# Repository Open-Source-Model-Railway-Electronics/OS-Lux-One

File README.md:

# OS-Lux-One

The OS-Lux-One is an open-source modular LED lighting strip for digital model railway systems 
It replaces multiple fixed-length coach strips with one universal version that can be shortened and reused for different coach types.
Each strip section contains its own current control to keep the light level steady, even when the track voltage changes.
The design is suitable for both H0 and N scale rolling stock.

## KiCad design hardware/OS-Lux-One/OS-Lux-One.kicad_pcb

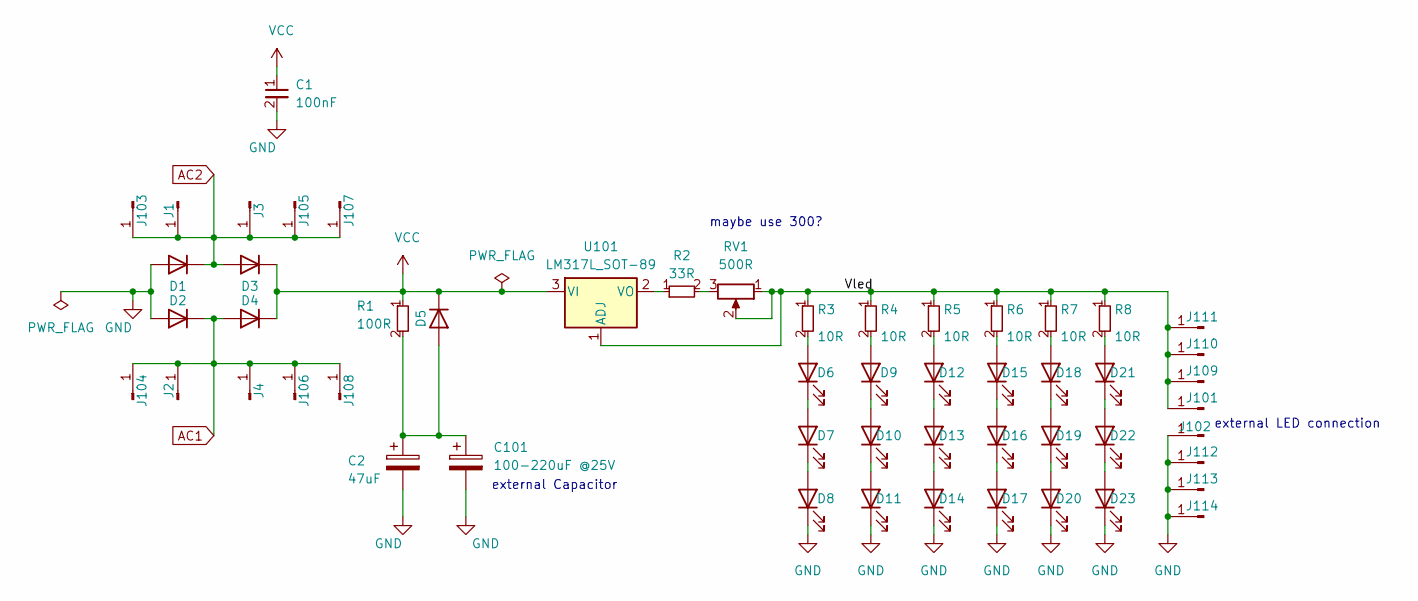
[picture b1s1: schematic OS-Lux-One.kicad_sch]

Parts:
C1: 100nF; C_0402_1005Metric; JLCPCB Part# C307331
C2: 47uF; CP_EIA-7343-31_Kemet-D; JLCPCB Part# C7228
C101: 100-220uF @25V; CP_Radial_D6.3mm_P2.50mm
D1, D2, D3, D4, D5: 1N4148WT; D_SOD-523; JLCPCB Part# C27748
D6, D7, D8, D9, D10, D11, D12, D13, D14, D15, D16, D17, D18, D19, D20, D21, D22, D23: LED; LED_0805_2012Metric; JLCPCB Part# C965820
J1, J2, J3, J4, J101, J102, J103, J104, J105, J106, J107, J108, J109, J110, J111, J112, J113, J114: Conn_01x01_Pin; 01_solderpad_2.54
R1: 100R; R_0603_smalltext; JLCPCB Part# C22775
R2: 33R; R_0603_smalltext; JLCPCB Part# C23140
R3, R4, R5, R6, R7, R8: 10R; R_0603_smalltext; JLCPCB Part# C22859
RV1: 500R; Potentiometer_Bourns_TC33X_Vertical; JLCPCB Part# C720649
U101: LM317L_SOT-89; SOT-89-3; JLCPCB Part# C5444280

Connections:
/Vled: J101.1, J109.1, J110.1, J111.1, R3.1, R4.1, R5.1, R6.1, R7.1, R8.1, RV1.1, RV1.2, U101.1 (ADJ); also elsewhere on the board
AC1: D2.1 (K), D4.2 (A), J2.1, J4.1, J104.1, J106.1, J108.1; also elsewhere on the board
AC2: D1.1 (K), D3.2 (A), J1.1, J3.1, J103.1, J105.1, J107.1; also elsewhere on the board
GND: C1.2, C2.2, C101.2, D1.2 (A), D2.2 (A), D8.1 (K), D11.1 (K), D14.1 (K), D17.1 (K), D20.1 (K), D23.1 (K), J102.1, J112.1, J113.1, J114.1; also elsewhere on the board
unnamed: C2.1, C101.1, D5.2 (A), R1.2
unnamed: D6.2 (A), R3.2
unnamed: D6.1 (K), D7.2 (A)
unnamed: D7.1 (K), D8.2 (A)
unnamed: D9.2 (A), R4.2
unnamed: D9.1 (K), D10.2 (A)
unnamed: D10.1 (K), D11.2 (A)
unnamed: D12.2 (A), R5.2
unnamed: D12.1 (K), D13.2 (A)
unnamed: D13.1 (K), D14.2 (A)
unnamed: D15.2 (A), R6.2
unnamed: D15.1 (K), D16.2 (A)
unnamed: D16.1 (K), D17.2 (A)
unnamed: D18.2 (A), R7.2
unnamed: D18.1 (K), D19.2 (A)
unnamed: D19.1 (K), D20.2 (A)
unnamed: D21.2 (A), R8.2
unnamed: D21.1 (K), D22.2 (A)
unnamed: D22.1 (K), D23.2 (A)
unnamed: R2.2, RV1.3
unnamed: R2.1, U101.2 (VO)
VCC: C1.1, D3.1 (K), D4.1 (K), D5.1 (K), R1.1, U101.3 (VI)

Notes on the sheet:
external Capacitor
external LED connection
maybe use 300?

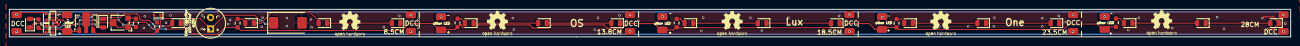
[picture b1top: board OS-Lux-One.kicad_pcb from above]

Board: 2 copper layers, 280.0 x 6.0 mm, 58 parts (0 on the bottom side), 26 nets.

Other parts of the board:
J107#2, J108#2: Conn_01x01_Pin; 01_solderpad_2.54
J109#2, J112#2: Conn_01x01_Pin

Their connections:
/Vled: J109#2.1; also elsewhere on the board
AC1: J108#2.1; also elsewhere on the board
AC2: J107#2.1; also elsewhere on the board
GND: J112#2.1; also elsewhere on the board

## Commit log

2025-10-26 added the OS-Lux-One
2025-10-26 altered manual for the OS-Lux-One
2025-11-15 upadted readme
